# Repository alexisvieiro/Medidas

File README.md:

# Medidas
Aislador-Girador repo

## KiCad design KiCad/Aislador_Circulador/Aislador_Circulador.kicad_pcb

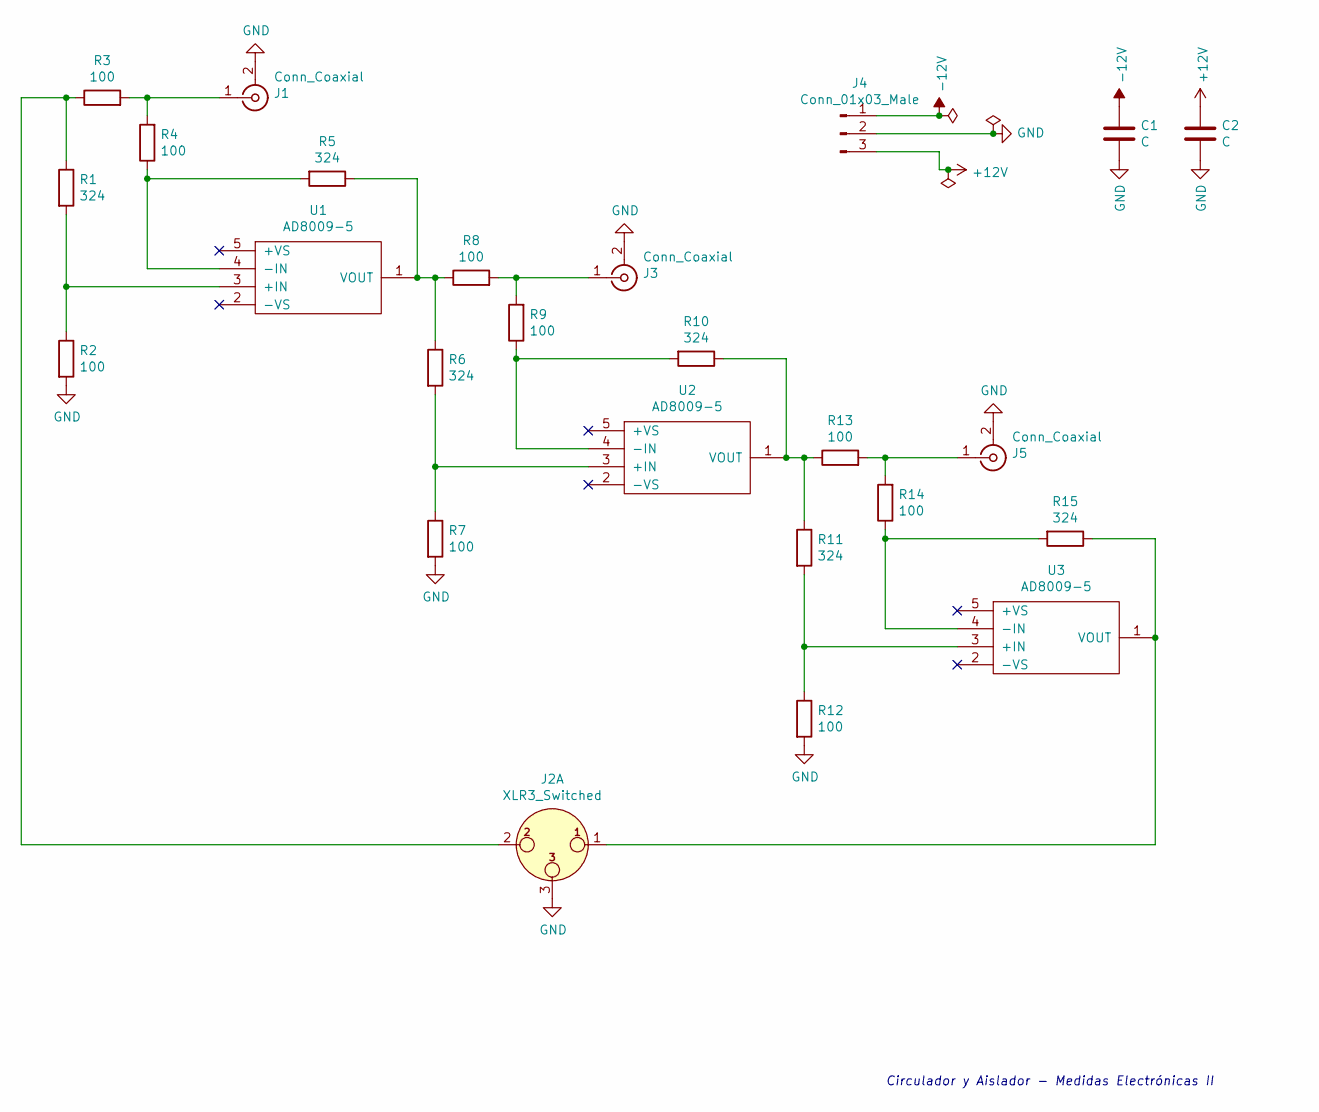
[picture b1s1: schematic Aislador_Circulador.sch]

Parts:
C1, C2: C; C_1206_3216Metric_Pad1.42x1.75mm_HandSolder
J1, J3, J5: Conn_Coaxial; SMA_Samtec_SMA-J-P-H-ST-EM1_EdgeMount
J2: XLR3_Switched; PinHeader_1x03_P2.00mm_Vertical
J4: Conn_01x03_Male; TerminalBlock_bornier-3_P5.08mm
R1, R5, R6, R10, R11, R15: 324; R_1206_3216Metric_Pad1.42x1.75mm_HandSolder
R2, R3, R4, R7, R8, R9, R12, R13, R14: 100; R_1206_3216Metric_Pad1.42x1.75mm_HandSolder
U1, U2, U3: AD8009-5; SOT-23-5_HandSoldering

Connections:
+12V: C2.1, J4.3
-12V: C1.1, J4.1
GND: C1.2, C2.2, J1.2 (Ext), J2.3, J3.2 (Ext), J4.2, J5.2 (Ext), R2.2, R7.2, R12.2
unnamed: J1.1 (In), R3.2, R4.2
unnamed: J2.1, R15.1, U3.1 (VOUT)
unnamed: J2.2, R1.1, R3.1
unnamed: J3.1 (In), R8.2, R9.2
unnamed: J5.1 (In), R13.2, R14.2
unnamed: R1.2, R2.1, U1.3 (+IN)
unnamed: R4.1, R5.2, U1.4 (-IN)
unnamed: R5.1, R6.1, R8.1, U1.1 (VOUT)
unnamed: R6.2, R7.1, U2.3 (+IN)
unnamed: R10.1, R11.1, R13.1, U2.1 (VOUT)
unnamed: R9.1, R10.2, U2.4 (-IN)
unnamed: R11.2, R12.1, U3.3 (+IN)
unnamed: R14.1, R15.2, U3.4 (-IN)

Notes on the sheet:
Circulador y Aislador - Medidas Electrónicas II

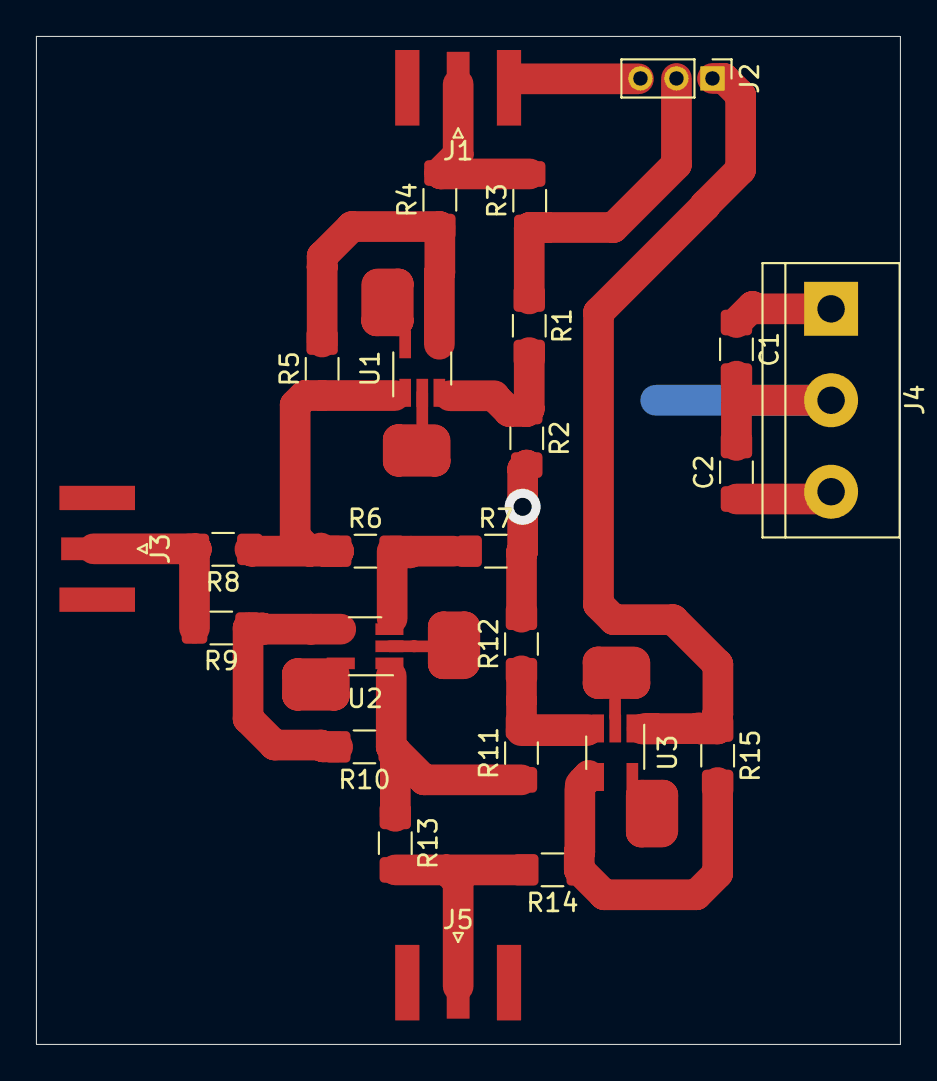
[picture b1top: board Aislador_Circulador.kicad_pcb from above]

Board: 2 copper layers, 48.0 x 56.0 mm, 25 parts (0 on the bottom side), 16 nets.

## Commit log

2019-09-30 pcb and pdf added
